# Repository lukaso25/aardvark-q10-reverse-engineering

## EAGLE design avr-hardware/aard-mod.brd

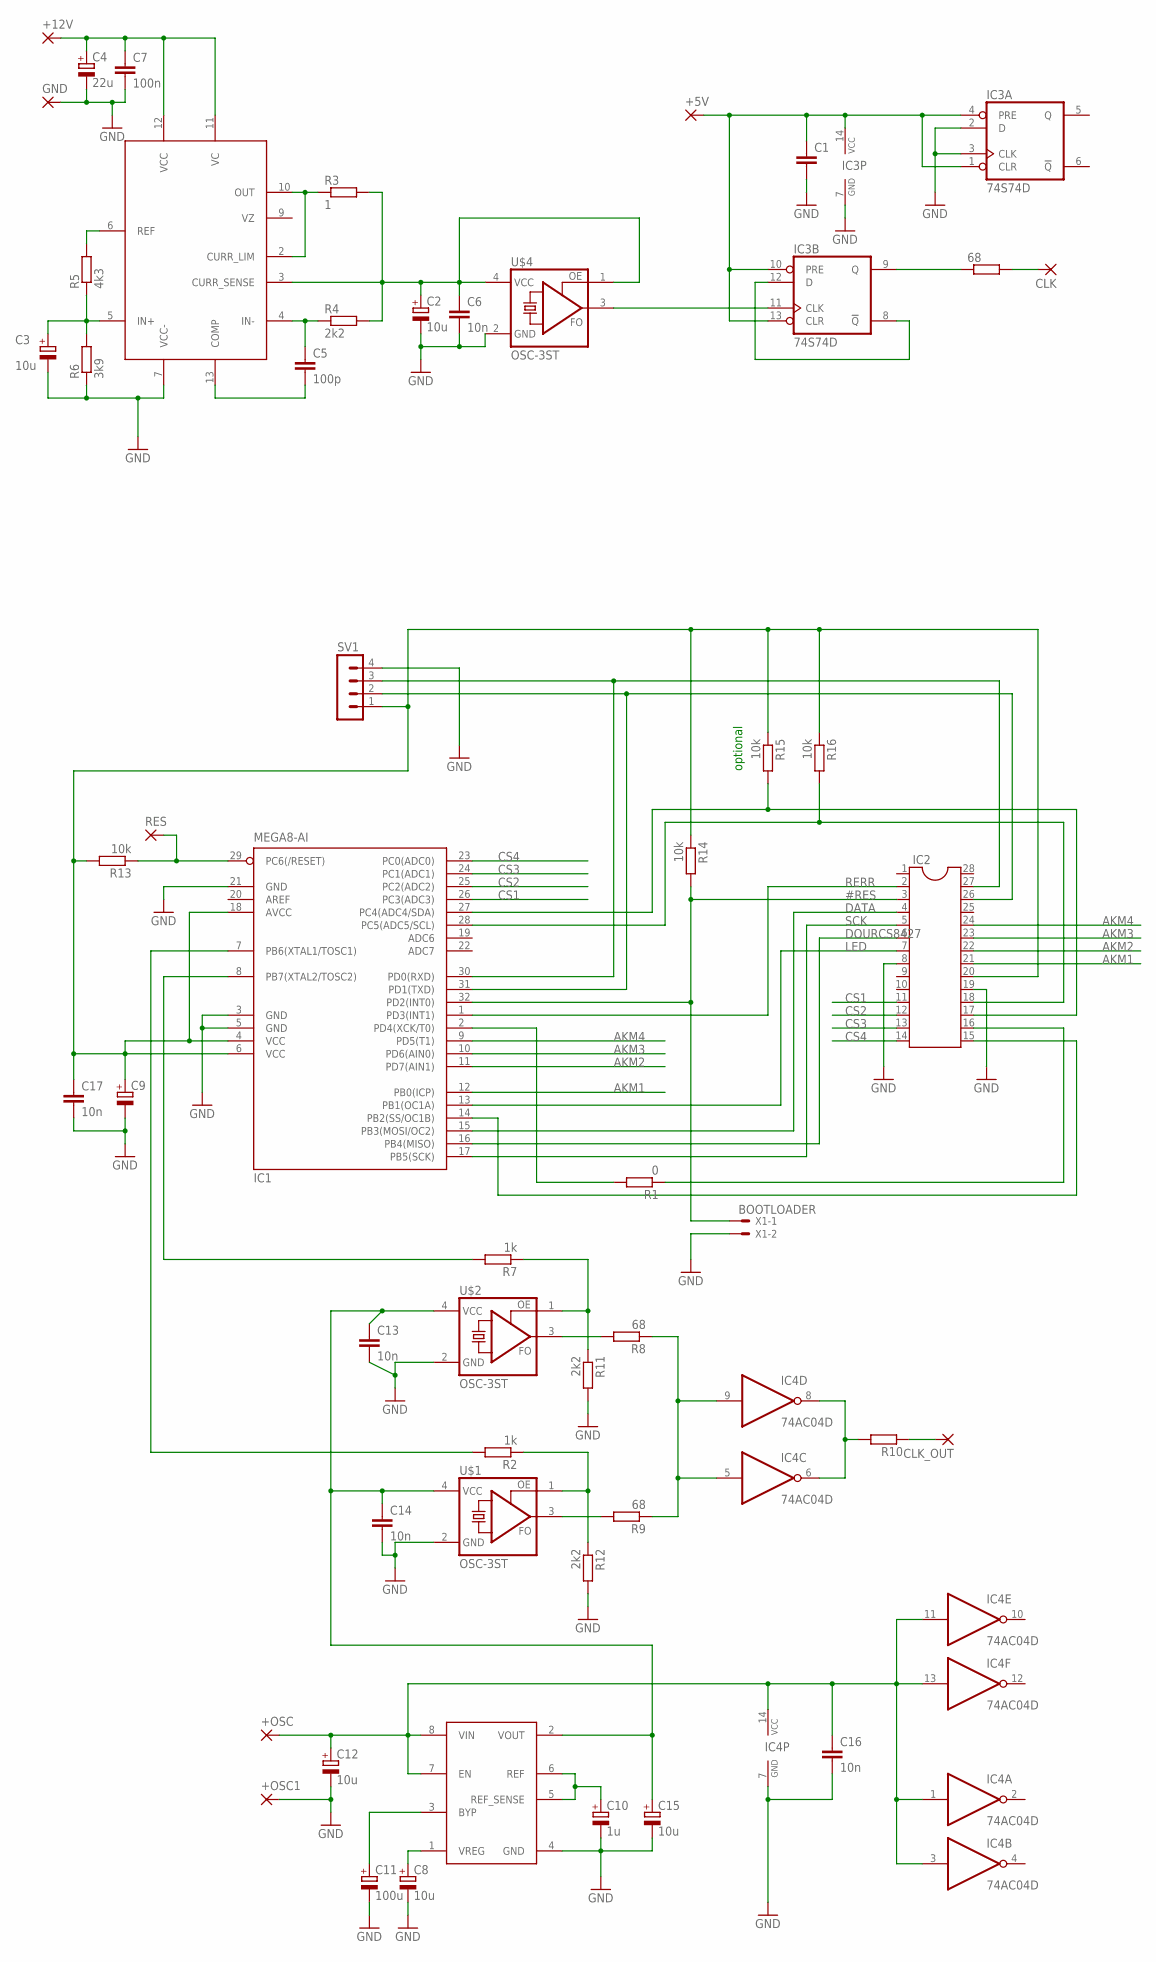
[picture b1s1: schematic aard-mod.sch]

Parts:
68: R-EU_M1206; M1206
+5V, +12V: 2,54/1,0
+OSC, +OSC1: 2,54/1,0
C1: C-EUC1206K; C1206K
C2, C8, C15: 10u; SMC_B
C3, C12: 10u; SMC_D
C4: 22u; SMC_D
C5: 100p; C0805K
C6, C17: 10n; C0805K
C7: 100n; C1206K
C9: CPOL-EUSMCB; SMC_B
C10: 1u; SMC_B
C11: 100u; SMC_D
C13, C14, C16: 10n; C1206
CLK: 2,54/1,0
CLK_OUT: 2,54/1,0
GND: 2,54/1,0
IC1: MEGA8-AI; TQFP32-08
IC2: DIL28-3
IC3: 74S74D; SO14
IC4: 74AC04D; SO14
R1: 0; R1206
R2, R7: 1k; R1206
R3: 1; M1206
R4, R11, R12: 2k2; R0805
R5: 4k3; R0805
R6: 3k9; R0805
R8, R9: 68; R1206
R10: R-EU_R0805; R0805
R13, R14, R15, R16: 10k; R1206
RES: 2,54/1,0
SV1: MA04-1
U$1, U$2, U$4: OSC-3ST; OSC2X2.5
U$3: 723; SO14
U$5: ADM7150; SO8-COOL
X1: BOOTLOADER; 22-23-2021

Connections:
5V: +12V.1, C4.+, C7.1, U$3.11 (VC), U$3.12 (VCC)
#RES: IC1.32 (PD2(INT0)), IC2.3, R14.2, X1.1
AKM1: IC1.12 (PB0(ICP)), IC2.21
AKM2: IC1.11 (PD7(AIN1)), IC2.22
AKM3: IC1.10 (PD6(AIN0)), IC2.23
AKM4: IC1.9 (PD5(T1)), IC2.24
CS1: IC1.26 (PC3(ADC3)), IC2.11
CS2: IC1.25 (PC2(ADC2)), IC2.12
CS3: IC1.24 (PC1(ADC1)), IC2.13
CS4: IC1.23 (PC0(ADC0)), IC2.14
DATA: IC1.15 (PB3(MOSI/OC2)), IC2.4
DOURCS8427: IC1.16 (PB4(MISO)), IC2.6
GND: +OSC1.1, C1.2, C2.-, C3.-, C4.-, C6.2, C7.2, C8.-, C9.-, C10.-, C11.-, C12.-, C13.2, C14.2, C15.-, C16.2, C17.2, GND.1, IC1.3 (GND), IC1.5 (GND), IC1.21 (GND), IC2.8, IC2.19, IC3.2 (D), IC3.3 (CLK), IC3.7 (GND), IC4.7 (GND), R6.1, R11.2, R12.2, SV1.4, U$1.2 (GND), U$2.2 (GND), U$3.7 (VCC-), U$4.2 (GND), U$5.4 (GND), X1.2
LED: IC1.13 (PB1(OC1A)), IC2.7
unnamed: IC1.2 (PD4(XCK/T0)), R1.2
unnamed: IC1.14 (PB2(SS/OC1B)), IC2.15
unnamed: IC1.28 (PC5(ADC5/SCL)), IC2.18, R16.2
unnamed: IC1.27 (PC4(ADC4/SDA)), IC2.17, R15.2
unnamed: IC1.30 (PD0(RXD)), IC2.27, SV1.3
unnamed: IC1.8 (PB7(XTAL2/TOSC2)), R7.2
unnamed: IC1.31 (PD1(TXD)), IC2.26, SV1.2
unnamed: IC2.16, R1.1
unnamed: IC1.7 (PB6(XTAL1/TOSC1)), R2.2
unnamed: C10.+, U$5.5 (REF_SENSE), U$5.6 (REF)
unnamed: C8.+, U$5.1 (VREG)
unnamed: C11.+, U$5.3 (BYP)
unnamed: +OSC.1, C12.+, C16.1, IC4.1 (I), IC4.3 (I), IC4.11 (I), IC4.13 (I), IC4.14 (VCC), U$5.7 (EN), U$5.8 (VIN)
unnamed: C13.1, C14.1, C15.+, U$1.4 (VCC), U$2.4 (VCC), U$5.2 (VOUT)
unnamed: C9.+, C17.1, IC1.4 (VCC), IC1.6 (VCC), IC1.18 (AVCC), IC2.20, R13.2, R14.1, R15.1, R16.1, SV1.1
unnamed: IC3.8 (!Q), IC3.12 (D)
unnamed: IC3.11 (CLK), U$4.3 (FO)
unnamed: +5V.1, C1.1, IC3.1 (CLR), IC3.4 (PRE), IC3.10 (PRE), IC3.13 (CLR), IC3.14 (VCC)
unnamed: IC4.6 (O), IC4.8 (O), R10.2
unnamed: CLK_OUT.1, R10.1
unnamed: C5.2, U$3.13 (COMP)
unnamed: R3.1, U$3.2 (CURR_LIM), U$3.10 (OUT)
unnamed: C5.1, R4.1, U$3.4 (IN-)
unnamed: C2.+, C6.1, R3.2, R4.2, U$3.3 (CURR_SENSE), U$4.1 (OE), U$4.4 (VCC)
unnamed: R5.2, U$3.6 (REF)
unnamed: C3.+, R5.1, R6.2, U$3.5 (IN+)
unnamed: R8.2, U$2.3 (FO)
unnamed: R7.1, R11.1, U$2.1 (OE)
unnamed: R2.1, R12.1, U$1.1 (OE)
unnamed: 68.2, CLK.1
unnamed: R9.2, U$1.3 (FO)
unnamed: IC4.5 (I), IC4.9 (I), R8.1, R9.1
unnamed: IC1.29 (PC6(/RESET)), R13.1, RES.1
unnamed: 68.1, IC3.9 (Q)
RERR: IC1.1 (PD3(INT1)), IC2.2
SCK: IC1.17 (PB5(SCK)), IC2.5

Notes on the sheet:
optional

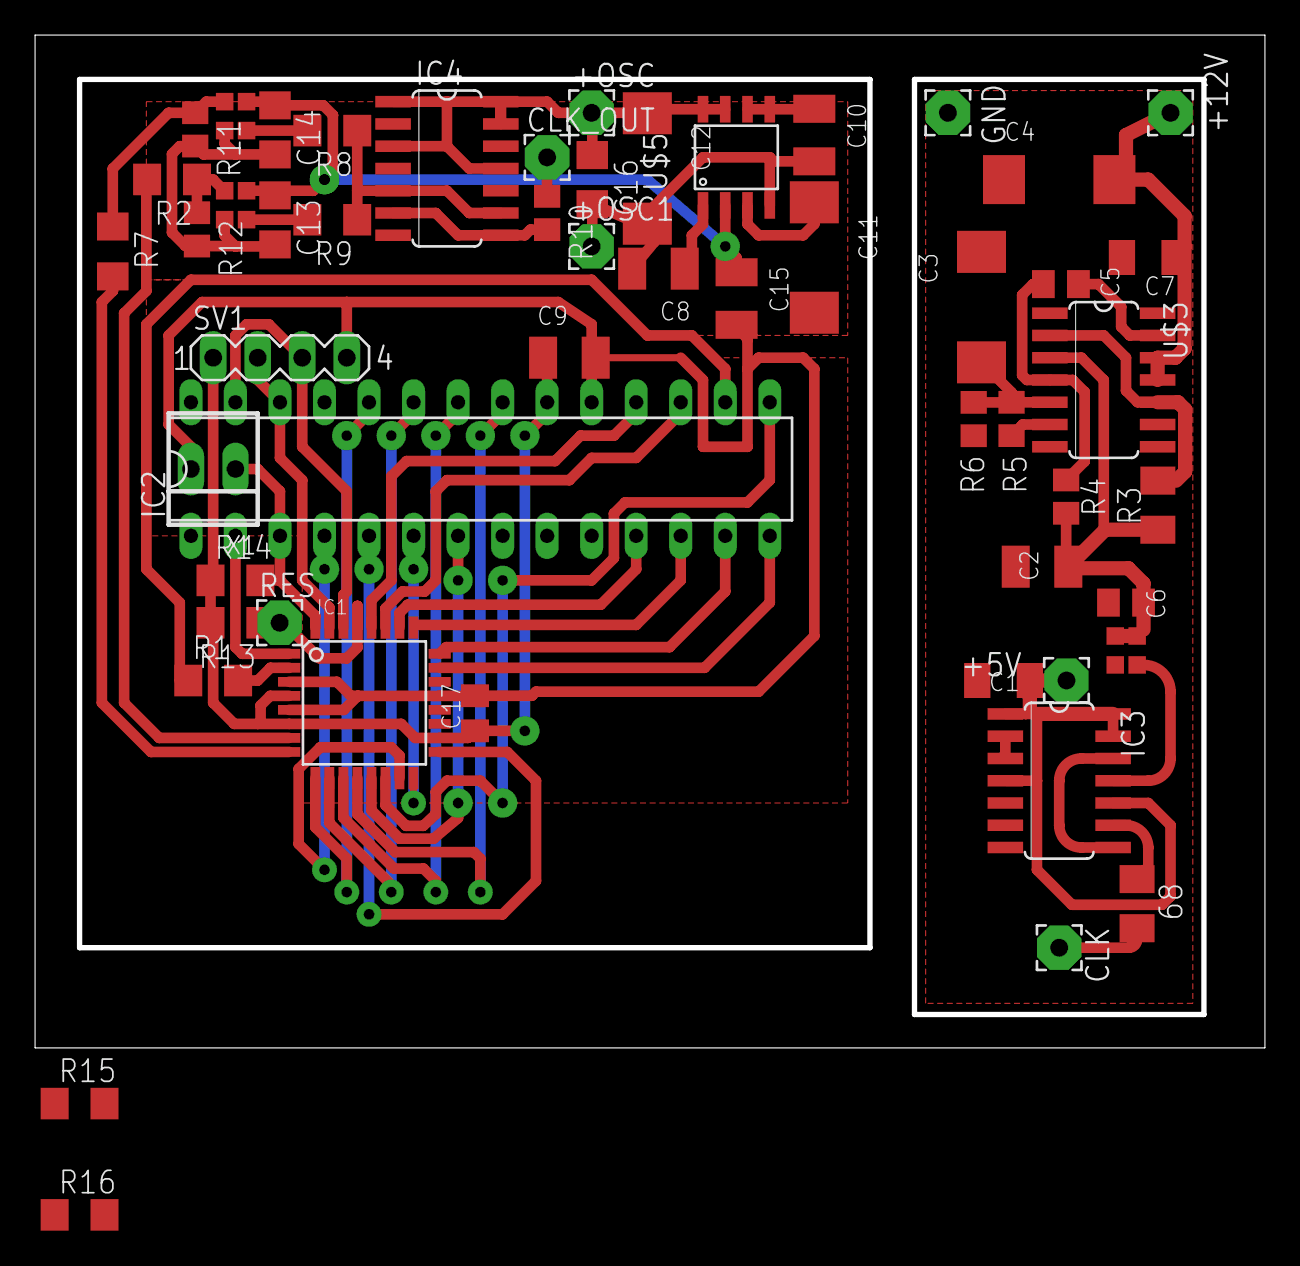
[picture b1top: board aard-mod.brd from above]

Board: 2 copper layers, 70.2 x 57.8 mm, 53 parts (0 on the bottom side), 50 nets.

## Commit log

2014-07-11 external module pinout
2014-09-03 Pinout png file
2015-03-29 PCB design - AVR mod board
    Eagle source files for modification PCB. This PCB substitutes
    functionality of original PIC microcontroller. PCB contains also low
    jitter clock oscilators.
2015-03-29 code for AVR microcontroller added
    I2C slave device, only testing code with lot of debugging sections,
    skeleton of Ardvark hardware initialization and configuration
2016-02-03 changes in code, debug LCD, test program for littewire usb i2c interface
2021-02-16 MIDI CC parsing added
2021-03-02 input gain switch test added
